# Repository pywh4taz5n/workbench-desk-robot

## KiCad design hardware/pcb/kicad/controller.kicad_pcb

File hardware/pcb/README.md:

# Controller PCB engineering package

Eight-layer controller/power-distribution board for a 48 V desk robot. The package
defines the electrical architecture, interfaces, protection, isolated CAN,
stackup, placement/thermal constraints, DFM limits, and manufacturing outputs.

## Reproduce checks

```bash
python hardware/pcb/tools/electrical_checks.py
```

The report is written to `generated/electrical_report.json`. Open
`kicad/controller.kicad_pro` with KiCad 10. The detailed EVT companion board has
117 controlled electrical components, four M3 NPTH mounting holes (121 total
footprints), fifteen SMT test pads, more than 1,300 track/via items, 31 filled copper zones,
eight copper layers, and a physical 8 mm primary/secondary isolation region.
Reproduce the controlled sources with:

```bash
<kicad>/bin/python hardware/pcb/tools/generate_footprints.py
python hardware/pcb/tools/generate_kicad_schematic.py
python hardware/pcb/tools/generate_expected_connectivity.py
python hardware/pcb/tools/generate_bom.py
<kicad>/bin/python hardware/pcb/tools/generate_kicad_board.py --session hardware/pcb/kicad/controller.ses
python hardware/pcb/tools/electrical_checks.py
python hardware/pcb/tools/audit_connectivity.py
python hardware/pcb/tools/layout_audit.py
python hardware/pcb/tools/export_fabrication.py
python hardware/pcb/tools/release_readiness.py
```

The default command is a production-release gate and returns non-zero while
the PCB remains blocked. Use `--stage evt` for prototype-order gating or
`--stage structure` when you only need the repository engineering audit.

`kicad/controller.ses` is the checked Freerouting 2.3.0 routing session. The
board generator validates every footprint position against that session before
importing the checked routing branches. Deterministic cleanup and local
supplements preserve more than 1,000 segments while adding the U2/U7 and fixture-pad migration. A
stale session cannot silently attach to moved footprints.
Generated schematic UUIDs use a resettable deterministic sequence. Board output
UUIDs are normalized after KiCad saves the file, preserving repeated references
while removing run-to-run UUID noise; routing tie-breakers use stable reference,
pad, and coordinate keys rather than process memory addresses.

The layout audit hard-gates the Q36SR U2 input, return, `12V_ISO` source and
`GND` return with separate eight-via rings on 3 x 3, 1.5 mm-pitch grids around
the THT pads, along with nominal-width coverage and bounded package escapes.
The exact 20 A manufacturer revision, lifecycle, quote, heat-spreader and AVL
remain procurement and thermal gates. The audit also requires top-layer, zero-via
oscillator routing, matched CAN via counts, and an `In1.Cu` `GND_CAN_ISO` zone
declaration. NXF1 U7 has an all-eight-layer no-track/no-via/no-pour corridor
across its 4.08 mm board pad-edge gap; this does not satisfy the 8 mm system
target or replace Safety Owner review.
CAN coupling, branch/stub geometry, reference-plane continuity, and 120 ohm field
solving remain explicit manual or supplier risks rather than being inferred from
aggregate route lengths. The report now includes per-net graph metrics, declared
reference-zone endpoint coverage, reference-layer low-speed occupancy, oscillator
length delta and load-capacitor ground-via distance, plus every accepted power-net
neckdown. These measurements bound the review; they do not claim field-solved
impedance, uninterrupted filled copper, or thermal adequacy.

Test access is separated by electrical domain: TP1 remains in the 48 V primary
region, TP2-TP5/TP8 are on the logic side, and TP6/TP7 sit beside the isolated
CAN connectors. This keeps secondary probes out of the primary test area and
avoids long CAN test stubs.
`fixture-access-plan.csv` controls the additional safety, power-good, fault,
current-monitor, and domain-reference access required by the EVT fixture. Existing
connector access is cross-checked against `connector-pinout.csv`; TP9-TP15 are
implemented as dedicated pads while every row remains fail-closed until physical
fixture evidence is attached.

The checked-in ERC and DRC reports contain zero violations and zero unconnected
items. Gerbers, drills, IPC-D-356, position data, drawings, statistics, and a
rendered inspection preview are under `fabrication/`.
`kicad/controller.kicad_dru` enforces 8 mm copper clearance between the primary
48 V domain and every non-primary net; release readiness fails if this rule is
missing even when the base DRC report is otherwise clean.

## Critical design-review correction

The original task suggestion (`TPS54160 + RT8059 + AMS1117`) is not load-capable:

- TPS54160 is a 1.5 A regulator and cannot supply the proposed 12 V motor rail.
- RT8059 is a low-current converter and cannot supply a 5 V / 8 A Jetson rail.
- AMS1117 cannot provide 3.3 V / 5 A and would exceed its thermal limit.

The baseline therefore requires a protected 48 V input and an isolated,
regulated 36-60 V-to-12 V 240 W-class module, followed by a protected 12 V / 5 A
branch to the Jetson developer-kit DC
input, and a 12-to-3.3 V 20 W synchronous buck. It deliberately does not
back-power the developer kit through a 5 V header. Design candidates are listed
in the fabrication BOM; purchase requires all independent Electrical,
Procurement, Safety and other roles named in the approval registers. System
Owner authorization alone does not create an AVL.

U2 is the `Q36SR12020NRFH` design candidate. Distributor evidence identifies
18-75 V input, 12 V/20 A and 240 W, and the checked eight-pin footprint follows
the Q36SR family mechanical drawing. The local Delta PDF is for the 12 V/19 A
variant and cannot close exact 20 A procurement evidence. `DCM3623T50M31C2T00`
remains excluded by its 16-50 V input, 28 V output and incompatible package.

The board is a companion/control board for the NVIDIA developer kit, not a raw
260-pin Jetson module carrier. See `interface-control.md` and
`source-baseline.json` for controlled interfaces, official sources, assumptions,
owners, and freeze gates. J4 is populated on this board; J7-J9 describe downstream
harness or daughterboard endpoints and are not populated in revision A.
The ISO1042 bus side uses distinct `5V_CAN_ISO` and `GND_CAN_ISO` nets supplied
by U7; neither is tied to logic ground in the board database.
The populated J4 backplane carries the external `JETSON_ENABLE_REQ` on pin 8;
it is an MCU input and is deliberately distinct from the internal
`MOTOR_ENABLE_REQ` generated on U5 pin 53. The E-stop path has distinct
`MOTOR_ENABLE_REQ` and `MOTOR_ENABLE_SAFE` nets,
a dual-channel J10 loop, dual-channel manual reset at J12, diagnostic isolation
at U8, force-guided relay candidates K1/K2, and the J11 gated output.
`connector-pinout.csv` freezes the current EVT pin mapping.
`connectors.csv` separates contact capability from the controlled system
envelope: J2 contacts are a 16 A nominal interface, but the board and harness
are limited to 10 A aggregate (120 W at 12 V) until an external branch fuse,
inrush, regeneration and fault-current analysis is approved.
`component-selection-matrix.csv` tracks every active module, the source-backed
candidate or class, verification method, owner and procurement status.
Every matrix `source_id` must resolve to a complete HTTPS source entry in
`source-baseline.json`; excluded-source records are retained as history and may
not back a design candidate.
`fabrication/bom.csv` covers every board component and its grouped lines are
recomputed deterministically. `component-approval-register.csv` defines the
required approver roles for every procurement-controlled group.
`component-approval-signatures.csv`
contains one independent row per required role, bound to the EVT revision and
fabrication-BOM SHA-256. No group is approved until every role records an
orderable MPN, datasheet revision, identity, date, and evidence reference.
Changing a summary `decision` to `APPROVED` is insufficient.
`expected-connectivity.json` and `generated/connectivity_report.json` independently
check the physical pads across all 117 controlled components, plus input-protection, CAN
isolation, current-sense and dual-channel safety invariants.
`testpoint-coverage.csv` defines the measurement, limit, instrument and required
evidence for every physical test pad.
`fabrication/bringup-test-plan.csv` covers 36 V, 48 V, and 60 V operation, UV/OV,
reverse polarity, branch short, load and regeneration transients, E-stop
discrepancy, CAN FD, and a four-hour closed-enclosure thermal soak. These are
controlled test definitions, not completed physical evidence.

Run `python hardware/pcb/tools/release_readiness.py` before sharing an order
package. The checked-in schematic is component-level and has clean ERC. EVT
prototype ordering remains blocked by AVL, safety design, supplier DFM and U2/U7
external evidence. Physical bring-up,
measured safety timing, harness execution, and verified fixture access are
separate production-release gates so prototype evidence is not a circular EVT
ordering prerequisite.
The release audit fails closed if stale U2 placeholder or excluded-part markers
appear in controlled artifacts, and separately reports whether exact manufacturer
evidence and AVL have closed.
Do not order a populated board from engineering completeness alone.

## Release status

PCB1-11 have reproducible engineering evidence. PCB12-18 have complete order,
bring-up, reliability, and production procedures but still require physical boards,
lab instruments, EMC facilities, and production operators; see the verification
matrix for the evidence that must be attached rather than inferred.

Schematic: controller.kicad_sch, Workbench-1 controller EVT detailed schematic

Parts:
C1: 1uF 100V; C_1210_3225Metric
C2: 10uF 100V; C_2220_5750Metric
C3: 470uF 25V; CP_Radial_D12.5mm_P5.00mm
C4: 1uF 25V; C_0805_2012Metric
C5: 220uF 25V; CP_Radial_D10.0mm_P5.00mm
C6: 22uF 25V; C_1210_3225Metric
C7, C8: 47uF 10V; C_1210_3225Metric
C9, C10, C11, C12, C13, C14, C15, C16, C18, C19, C40, C41, C44: 100nF; C_0603_1608Metric
C17, C42, C43: 4.7uF; C_0805_2012Metric
C20: 1uF 10V; C_0603_1608Metric
CG1: 4.7nF 100V; C_0603_1608Metric
CSS4: 22nF; C_0603_1608Metric
CY1, CY2: 18pF; C_0603_1608Metric
D1: SMCJ58A; D_SMC; MPN Littelfuse SMCJ58A
D2: CAN FD TVS; CAN_TVS; MPN Nexperia PESD2CANFD24V-T
D3, D4: FLYBACK; D_SOD-123; MPN Diodes Inc. 1N4148W-7-F
F1: 10A 125V; Fuse_4510; MPN Littelfuse 0451010.MRL
F2: PTC 0.25A; Fuse_1206_3216Metric; MPN Littelfuse 1206L025YR
J1: 48V INPUT; MicroFit_2x2; MPN Molex 43045-0412
J2: 12V MOTOR AUX; MicroFit_2x2; MPN Molex 43045-0412
J3: JETSON DEVKIT 12V; MicroFit_2x2; MPN Molex 43045-0412
J4: JETSON MCU BACKPLANE; PinHeader_2x10_P2.54mm_Vertical
J5: CAN A; MicroFit_2x2; MPN Molex 43045-0412
J6: CAN B; MicroFit_2x2; MPN Molex 43045-0412
J10: DUAL ESTOP LOOP; MicroFit_2x2; MPN Molex 43045-0412
J11: SAFETY OUTPUT; MicroFit_2x2; MPN Molex 43045-0412
J12: DUAL MANUAL RESET; MicroFit_2x2; MPN Molex 43045-0412
J13: WCH DEBUG; PinHeader_1x04_P2.54mm_Vertical
JP1: CAN TERM; PinHeader_1x02_P2.54mm_Vertical
K1: FORCE-GUIDED 12V A; Panasonic_SFM4; MPN Panasonic SFM4-DC12V
K2: FORCE-GUIDED 12V B; Panasonic_SFM4; MPN Panasonic SFM4-DC12V
L1: 100R@100MHz; ACT45B; MPN TDK ACT45B-101-2P-TL003
Q1, Q2: 150V N-MOS; Infineon_PG-TDSON-8_6.15x5.15mm; MPN Infineon BSC093N15NS5ATMA1
R30, R31, R32, R33, R34, R35, R36, R37, R38, R39, R40, R41, R42: 33R; R_0603_1608Metric
R43, R44, R45, R46, R57: 100k; R_0603_1608Metric
R47, R49, R50, R51, R54: 10k; R_0603_1608Metric
R48: 3.00k 1%; R_0603_1608Metric
R52, R53, R55, R56: 4.7k; R_0603_1608Metric
R58: 120R 1%; R_1206_3216Metric
R59: 73.2k 1%; R_0603_1608Metric
R60: 10.0k 1%; R_0603_1608Metric
RFB1: 45.0k 1%; R_0603_1608Metric
RFB2: 10.0k 1%; R_0603_1608Metric
RG1: 22k; R_0603_1608Metric
RPG1: 453k 1%; R_0603_1608Metric
RPG2: 56.0k 1%; R_0603_1608Metric
RPG3: 10k; R_0603_1608Metric
RS1: 6mR 3W 1%; Sense_3637; MPN Vishay WSL3637R0060FEA
RSH1: 510k; R_0603_1608Metric
RUV1: 19.6M 1%; R_1206_3216Metric
RUV2: 133k 1%; R_0603_1608Metric
RUV3: 162k 1%; R_0603_1608Metric
TP1: VBAT_PROTECTED; TestPoint_Pad_D1.5mm
TP2: 12V_ISO; TestPoint_Pad_D1.5mm
TP3: JETSON_12V; TestPoint_Pad_D1.5mm
TP4: 3V3_LOGIC; TestPoint_Pad_D1.5mm
TP5: GND; TestPoint_Pad_D1.5mm
TP6: CANH; TestPoint_Pad_D1.5mm
TP7: CANL; TestPoint_Pad_D1.5mm
TP8: MCU_RESET; TestPoint_Pad_D1.5mm
TP9: 5V_CAN_ISO; TestPoint_Pad_D1.5mm
TP10: 3V3_PGOOD; TestPoint_Pad_D1.5mm
TP11: JETSON_PGOOD; TestPoint_Pad_D1.5mm
TP12: JETSON_FAULT_N; TestPoint_Pad_D1.5mm
TP13: U3_IMON; TestPoint_Pad_D1.5mm
TP14: ESTOP_A_MON; TestPoint_Pad_D1.5mm
TP15: ESTOP_B_MON; TestPoint_Pad_D1.5mm
U1: LTC4368HMS-2; MSOP-10_3x3mm_P0.5mm; MPN LTC4368HMS-2#PBF
U2: 18-75V TO 12V 240W ISO; Delta_Q36SR_QuarterBrick; MPN Q36SR12020NRFH
U3: TPS26633RGE; TPS26633_RGE24; MPN Texas Instruments TPS26633RGER
U4: RPL-5.0 3V3/5A; RPL-5.0_QFN24; MPN RECOM RPL-5.0-R
U5: CH32V307VCT6; LQFP-100_14x14mm_P0.5mm; MPN WCH CH32V307VCT6
U6: ISO1042DW; ISO1042_DW16_HV; MPN Texas Instruments ISO1042DWR
U7: 3V3-5V ISO 1W; Murata_NXF1_MC; MPN NXF1S0305MC-R7
U8: ESTOP DIAGNOSTIC OPTO; SOIC-16W_7.5x10.3mm_P1.27mm; MPN Toshiba TLP293-4(GB,E)
Y1: 8MHz; Crystal_SMD_3225-4Pin_3.2x2.5mm; MPN Abracon ABM8-8.000MHZ-B2-T

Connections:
3V3_LOGIC: C7.1 (+), C8.1 (+), C9.1 (+), C10.1 (+), C11.1 (+), C12.1 (+), C13.1 (+), C14.1 (+), C15.1 (+), C16.1 (+), C17.1 (+), C40.1 (+), C42.1 (+), J4.1, J4.3, J11.4, J13.1, K1.5 (SENSE_COM), K1.9 (EDM_COM), K2.9 (EDM_COM), R47.1, R49.1, R50.1, R54.1, R55.1, R56.1, RFB1.1, RPG3.1, TP4.1, U3.12 (SHDN), U4.9 (VOUT), U4.10 (VOUT), U4.11 (VOUT), U4.12 (VOUT), U5.6 (VBAT), U5.11 (VDD), U5.21 (VREF+), U5.22 (VDDA), U5.28 (VDD), U5.50 (VIO), U5.75 (VDD), U5.100 (VIO), U6.1 (VCC1), U7.3 (+VIN)
3V3_PGOOD: TP10.1, U4.20 (PG), U4.21 (PG)
5V_CAN_ISO: C41.1 (+), C43.1 (+), C44.1 (+), TP9.1, U6.11 (VCC2), U6.16 (VCC2), U7.8 (+VOUT)
12V_ISO: C3.1 (+), C4.1 (+), C6.1 (+), F2.1 (IN), J2.1, J2.2, R46.1, R59.1, TP2.1, U2.7 (+SENSE), U2.8 (+VOUT), U3.1 (IN), U3.2 (IN), U3.5 (IN_SYS), U4.22 (VIN)
BOOT0: R43.1, U5.94 (BOOT0)
CANH: D2.1 (CANH), J5.1, J6.1, L1.4 (CANH_OUT), R58.1, TP6.1
CANH_RAW: L1.1 (CANH_IN), U6.13 (CANH)
CANL: D2.2 (CANL), J5.2, J6.2, JP1.2, L1.3 (CANL_OUT), TP7.1
CANL_RAW: L1.2 (CANL_IN), U6.12 (CANL)
CAN_RX: U5.81 (PD0/CAN1_RX), U6.5 (RXD)
CAN_TERM: JP1.1, R58.2
CAN_TX: U5.82 (PD1/CAN1_TX), U6.3 (TXD)
ESTOP_12V: F2.2 (OUT), J10.1, J10.3
ESTOP_A_MON: R49.2, TP14.1, U5.57 (PD10), U8.16 (C1)
ESTOP_B_MON: R50.2, TP15.1, U5.58 (PD11), U8.14 (C2)
ESTOP_CH_A_RETURN: J10.2, J12.1, K1.7 (HOLD_COM), U8.1 (A1)
ESTOP_CH_B_RETURN: J10.4, J12.3, K2.7 (HOLD_COM), U8.3 (A2)
ESTOP_SENSE: J4.17, J11.2, K2.6 (SENSE_NO), R57.1, U5.54 (PB15)
GND: C3.2 (-), C4.2 (-), C5.2 (-), C6.2 (-), C7.2 (-), C8.2 (-), C9.2 (-), C10.2 (-), C11.2 (-), C12.2 (-), C13.2 (-), C14.2 (-), C15.2 (-), C16.2 (-), C17.2 (-), C18.2 (-), C19.2 (-), C20.2 (-), C40.2 (-), C42.2 (-), CSS4.2 (-), CY1.2 (-), CY2.2 (-), D3.2 (A), D4.2 (A), J2.3, J2.4, J3.3, J3.4, J4.2, J4.4, J11.3, J13.4, K1.2 (COIL-), K2.2 (COIL-), R43.2, R44.2, R45.2, R48.2, R51.2, R52.2, R53.2, R57.2, R60.2, RFB2.2, RPG2.2, TP5.1, U2.4 (-VOUT), U2.5 (-SENSE), U3.7 (PLIM), U3.8 (GND), U3.25 (PowerPAD), U4.1 (PGND), U4.2 (PGND), U4.3 (PGND), U4.4 (PGND), U4.5 (PGND), U4.18 (AGND), U4.24 (PGND), U5.10 (VSS), U5.19 (VSSA), U5.20 (VREF-), U5.27 (VSS), U5.49 (VSS), U5.74 (VSS), U5.99 (VSS), U6.2 (GND1), U6.8 (GND1), U7.1 (-VIN), U8.13 (E2), U8.15 (E1)
GND_CAN_ISO: C41.2 (-), C43.2 (-), C44.2 (-), D2.3 (GND), D2.4 (GND), J5.3, J6.3, U6.9 (GND2), U6.10 (GND2), U6.15 (GND2), U7.7 (-VOUT)
GND_PWR: C1.2 (-), C2.2 (-), D1.2 (A), J1.3, J1.4, RUV3.2, U1.1 (GND), U1.2 (RETRY), U2.2 (ON/OFF), U2.3 (-VIN)
I2C_SCL: J4.16, R39.2, R55.2
I2C_SCL_MCU: R39.1, U5.92 (PB6/I2C1_SCL)
I2C_SDA: J4.15, R40.2, R56.2
I2C_SDA_MCU: R40.1, U5.93 (PB7/I2C1_SDA)
JETSON_12V: C5.1 (+), J3.1, J3.2, RPG1.1, TP3.1, U3.17 (OUT), U3.18 (OUT)
JETSON_ENABLE_REQ: J4.8, U5.91 (PB5)
JETSON_FAULT_N: R47.2, TP12.1, U3.14 (FLT)
JETSON_PGOOD: RPG3.2, TP11.1, U3.16 (PGOOD)
MCU_RESET: C19.1 (+), J4.20, R54.2, TP8.1, U5.14 (NRST)
MOTOR_CS0: J4.9, R33.2
MOTOR_CS0_MCU: R33.1, U5.35 (PB0)
MOTOR_CS1: J4.10, R34.2
MOTOR_CS1_MCU: R34.1, U5.36 (PB1)
MOTOR_CS2: J4.11, R35.2
MOTOR_CS2_MCU: R35.1, U5.47 (PB10)
MOTOR_CS3: J4.12, R36.2
MOTOR_CS3_MCU: R36.1, U5.48 (PB11)
MOTOR_CS4: J4.13, R37.2
MOTOR_CS4_MCU: R37.1, U5.51 (PB12)
MOTOR_CS5: J4.14, R38.2
MOTOR_CS5_MCU: R38.1, U5.52 (PB13)
MOTOR_ENABLE_REQ: K1.3 (SAFE_COM), U5.53 (PB14)
MOTOR_ENABLE_SAFE: J11.1, K2.4 (SAFE_NO)
OSC_IN: CY1.1 (+), U5.12 (OSC_IN), Y1.1
OSC_OUT: CY2.1 (+), U5.13 (OSC_OUT), Y1.2
OV_SET: RUV2.2, RUV3.1, U1.3 (OV)
RELAY_A_NC: K1.10 (EDM_NC), R44.1, U5.55 (PD8)
RELAY_B_NC: K2.10 (EDM_NC), R45.1, U5.56 (PD9)
RESET_CH_A_RETURN: D3.1 (K), J12.2, K1.1 (COIL+), K1.8 (HOLD_NO)
RESET_CH_B_RETURN: D4.1 (K), J12.4, K2.1 (COIL+), K2.8 (HOLD_NO)
SAFE_STAGE_A: K1.4 (SAFE_NO), K2.3 (SAFE_COM)
SENSE_STAGE_A: K1.6 (SENSE_NO), K2.5 (SENSE_COM)
SPI_MISO: J4.7, R32.2
SPI_MISO_MCU: R32.1, U5.31 (PA6/SPI1_MISO)
SPI_MOSI: J4.6, R31.2
SPI_MOSI_MCU: R31.1, U5.32 (PA7/SPI1_MOSI)
SPI_SCLK: J4.5, R30.2
SPI_SCLK_MCU: R30.1, U5.30 (PA5/SPI1_SCK)
SWCLK: J13.3, U5.76 (SWCLK)
SWDIO: J13.2, U5.72 (SWDIO)
U1_GATE: RG1.1, U1.10 (GATE)
U1_SHDN: RSH1.2, U1.6 (SHDN)
U3_DVDT: C18.1 (+), U3.9 (dVdT)
U3_ILIM: R48.1, U3.10 (ILIM)
U3_IMON: R51.1, TP13.1, U3.13 (IMON)
U3_PGTH: RPG1.2, RPG2.1, U3.15 (PGTH)
U3_UVLO: R59.2, R60.1, U3.6 (UVLO)
U4_CTRL: R46.2, U4.16 (CTRL)
U4_FB: RFB1.2, RFB2.1, U4.17 (FB)
U4_SS: CSS4.1 (+), U4.19 (SS)
U4_VCC: C20.1 (+), U4.6 (VCC)
U8_LED_A_K: R52.1, U8.2 (K1)
U8_LED_B_K: R53.1, U8.4 (K2)
UART_RX: J4.19, R42.2
UART_RX_MCU: R42.1, U5.69 (PA10/USART1_RX)
UART_TX: J4.18, R41.2
UART_TX_MCU: R41.1, U5.68 (PA9/USART1_TX)
UV_SET: RUV1.2, RUV2.1, U1.4 (UV)
VBAT_PROTECTED: C1.1 (+), C2.1 (+), RS1.2, TP1.1, U1.8 (VOUT), U2.1 (+VIN)
VBAT_RAW: F1.1 (IN), J1.1, J1.2

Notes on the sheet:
INPUT PROTECTION
ISOLATED POWER
JETSON EFUSE
3V3 POWER
POWER OUTPUTS
MCU AND BACKPLANE
ISOLATED CAN FD
HARDWIRED ESTOP
TEST ACCESS

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
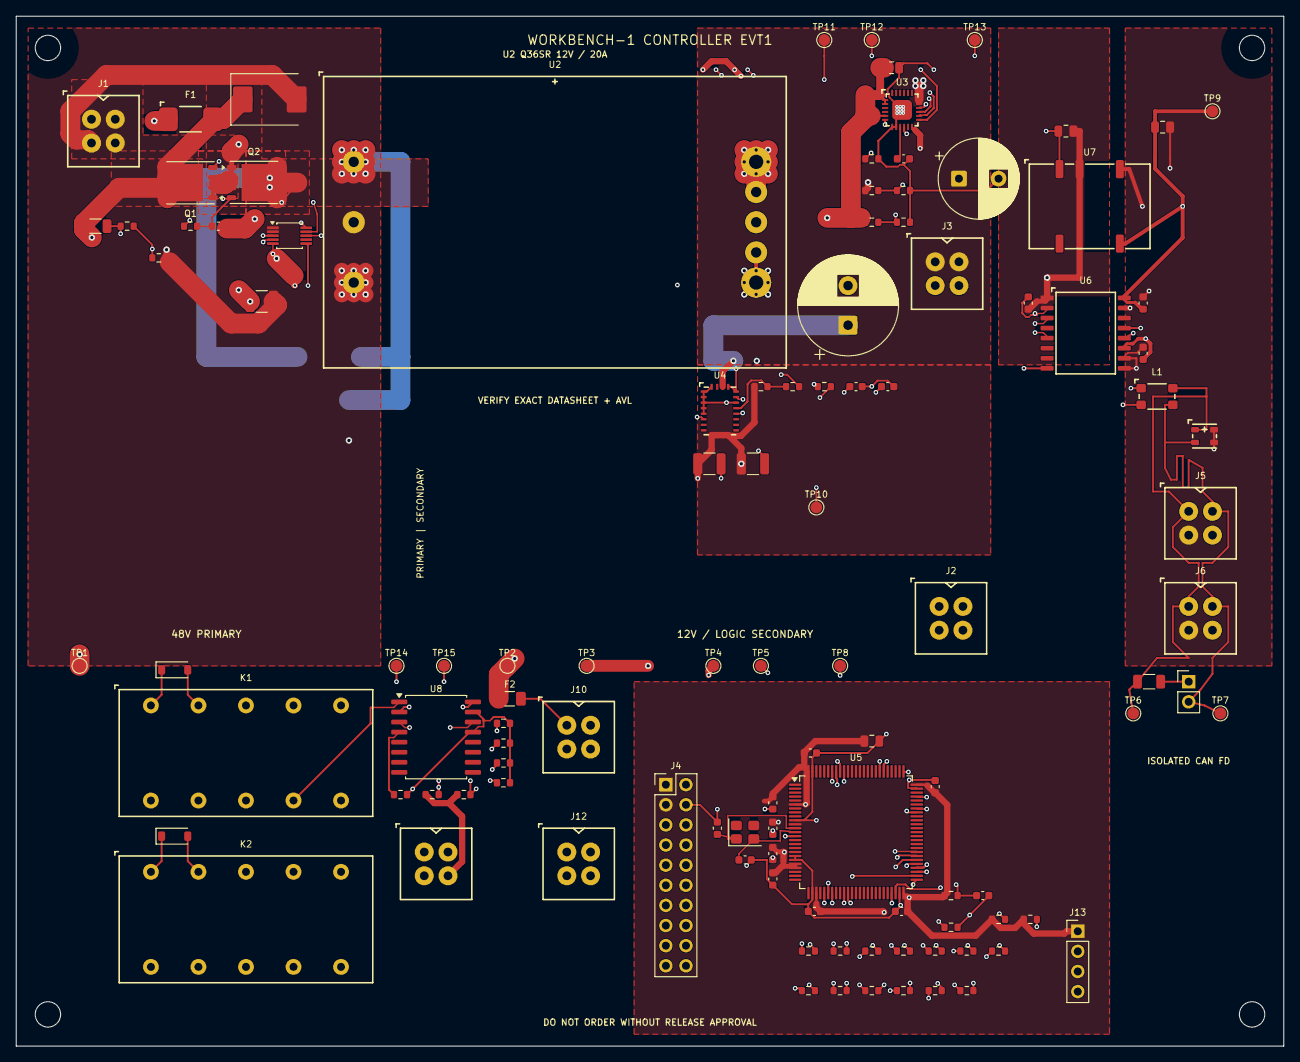
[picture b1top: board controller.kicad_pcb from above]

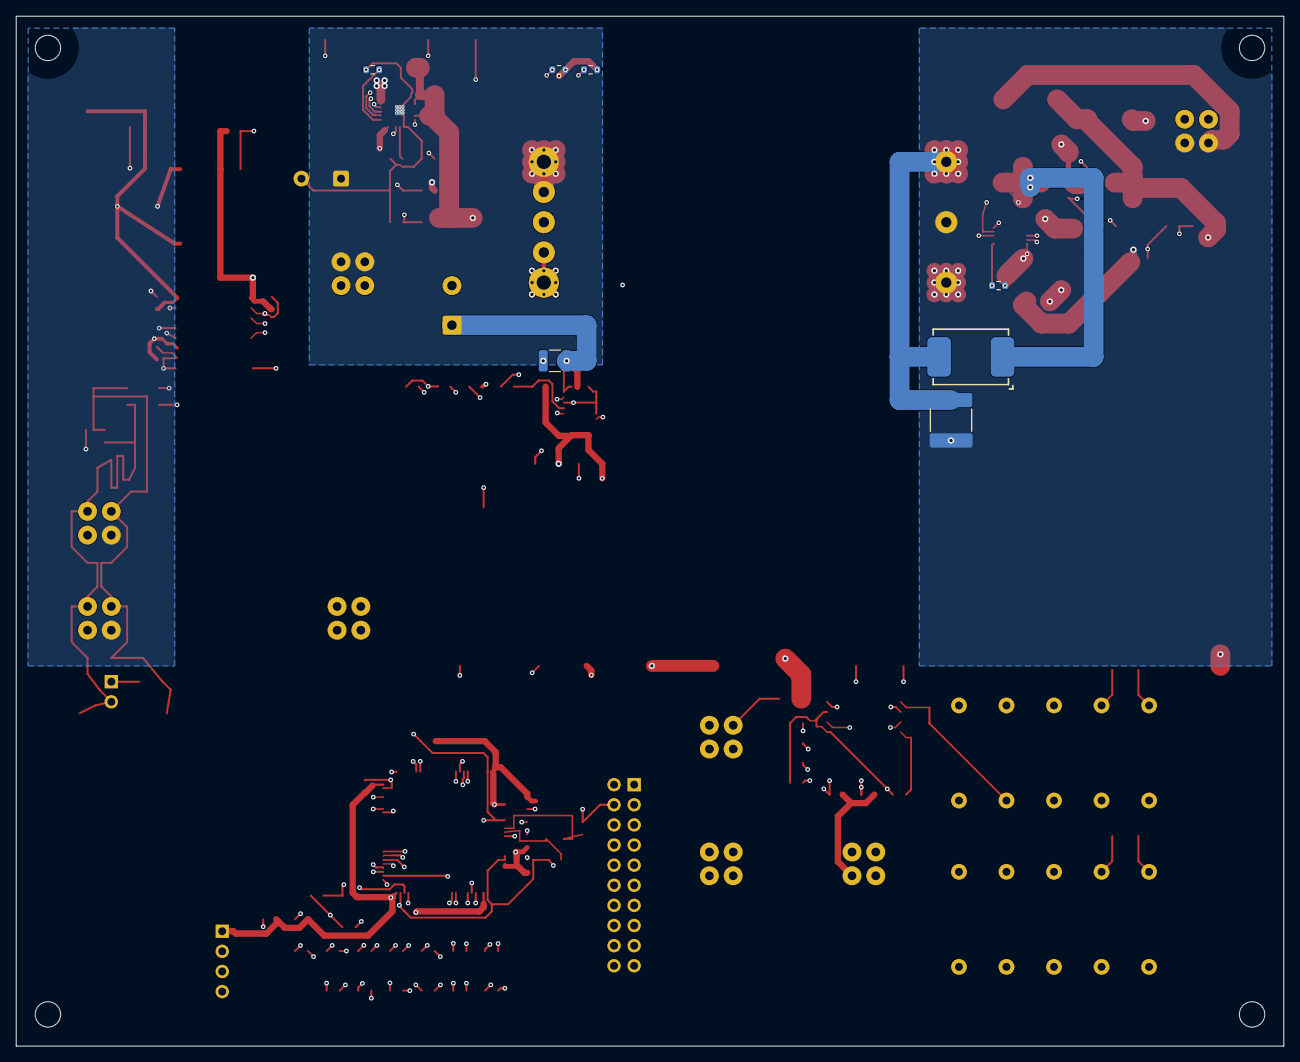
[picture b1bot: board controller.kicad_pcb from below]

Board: 8 copper layers, 160.0 x 130.0 mm, 121 parts (7 on the bottom side), 85 nets.

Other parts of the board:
H1, H2, H3, H4: M3_NPTH

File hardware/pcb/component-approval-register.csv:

reference,candidate,required_approver,decision,approved_mpn,datasheet_revision,approved_by,approved_at,evidence_ref
C1,1uF 100V; Capacitor_SMD:C_1210_3225Metric,Electrical + Procurement Owners,PENDING,,,,,
C2,10uF 100V; Capacitor_SMD:C_2220_5750Metric,Electrical + Procurement Owners,PENDING,,,,,
C3,470uF 25V; Capacitor_THT:CP_Radial_D12.5mm_P5.00mm,Electrical + Procurement Owners,PENDING,,,,,
C4,1uF 25V; Capacitor_SMD:C_0805_2012Metric,Electrical + Procurement Owners,PENDING,,,,,
C5,220uF 25V; Capacitor_THT:CP_Radial_D10.0mm_P5.00mm,Electrical + Procurement Owners,PENDING,,,,,
C6,22uF 25V; Capacitor_SMD:C_1210_3225Metric,Electrical + Procurement Owners,PENDING,,,,,
C7 C8,47uF 10V; Capacitor_SMD:C_1210_3225Metric,Electrical + Procurement Owners,PENDING,,,,,
C9 C10 C11 C12 C13 C14 C15 C16 C19,100nF; Capacitor_SMD:C_0603_1608Metric,Firmware + Electrical + Procurement Owners,PENDING,,,,,
C17,4.7uF; Capacitor_SMD:C_0805_2012Metric,Firmware + Electrical + Procurement Owners,PENDING,,,,,
C18,100nF; Capacitor_SMD:C_0603_1608Metric,Electrical + Procurement Owners,PENDING,,,,,
C20,1uF 10V; Capacitor_SMD:C_0603_1608Metric,Electrical + Procurement Owners,PENDING,,,,,
C40 C41 C44,100nF; Capacitor_SMD:C_0603_1608Metric,Electrical + Procurement Owners,PENDING,,,,,
C42 C43,4.7uF; Capacitor_SMD:C_0805_2012Metric,Electrical + Procurement Owners,PENDING,,,,,
CG1,4.7nF 100V; Capacitor_SMD:C_0603_1608Metric,Electrical + Procurement Owners,PENDING,,,,,
CSS4,22nF; Capacitor_SMD:C_0603_1608Metric,Electrical + Procurement Owners,PENDING,,,,,
CY1 CY2,18pF; Capacitor_SMD:C_0603_1608Metric,Firmware + Electrical + Procurement Owners,PENDING,,,,,
D1,Littelfuse SMCJ58A,Electrical + Procurement Owners,PENDING,,,,,
D2,Nexperia PESD2CANFD24V-T,Electrical + Procurement Owners,PENDING,,,,,
D3 D4,Diodes Inc. 1N4148W-7-F,Safety + Electrical + Procurement Owners,PENDING,,,,,
F1,Littelfuse 0451010.MRL,Electrical + Procurement Owners,PENDING,,,,,
F2,Littelfuse 1206L025YR,Safety + Electrical + Procurement Owners,PENDING,,,,,
J1,Molex 43045-0412,System + Electrical + Procurement Owners,PENDING,,,,,
J2,Molex 43045-0412,Electrical + Procurement Owners,PENDING,,,,,
J3,Molex 43045-0412,System + Electrical + Procurement Owners,PENDING,,,,,
J4,JETSON MCU BACKPLANE; Connector_PinHeader_2.54mm:PinHeader_2x10_P2.54mm_Vertical,Firmware + Electrical + Procurement Owners,PENDING,,,,,
J5,Molex 43045-0412,Electrical + Procurement Owners,PENDING,,,,,
J6,Molex 43045-0412,Electrical + Procurement Owners,PENDING,,,,,
J10,Molex 43045-0412,Safety + Electrical + Procurement Owners,PENDING,,,,,
J11,Molex 43045-0412,Safety + Electrical + Procurement Owners,PENDING,,,,,
J12,Molex 43045-0412,Safety + Electrical + Procurement Owners,PENDING,,,,,
J13,WCH DEBUG; Connector_PinHeader_2.54mm:PinHeader_1x04_P2.54mm_Vertical,Firmware + Electrical + Procurement Owners,PENDING,,,,,
JP1,CAN TERM; Connector_PinHeader_2.54mm:PinHeader_1x02_P2.54mm_Vertical,Electrical + Procurement Owners,PENDING,,,,,
K1,Panasonic SFM4-DC12V,Safety + Electrical + Procurement Owners,PENDING,,,,,
K2,Panasonic SFM4-DC12V,Safety + Electrical + Procurement Owners,PENDING,,,,,
L1,TDK ACT45B-101-2P-TL003,Electrical + Procurement Owners,PENDING,,,,,
Q1 Q2,Infineon BSC093N15NS5ATMA1,Electrical + Procurement Owners,PENDING,,,,,
R30 R31 R32 R33 R34 R35 R36 R37 R38 R39 R40 R41 R42,33R; Resistor_SMD:R_0603_1608Metric,Firmware + Electrical + Procurement Owners,PENDING,,,,,
R43,100k; Resistor_SMD:R_0603_1608Metric,Firmware + Electrical + Procurement Owners,PENDING,,,,,
R44 R45 R57,100k; Resistor_SMD:R_0603_1608Metric,Safety + Electrical + Procurement Owners,PENDING,,,,,
R46,100k; Resistor_SMD:R_0603_1608Metric,Electrical + Procurement Owners,PENDING,,,,,
R47 R51 RPG3,10k; Resistor_SMD:R_0603_1608Metric,Electrical + Procurement Owners,PENDING,,,,,
R48,3.00k 1%; Resistor_SMD:R_0603_1608Metric,Electrical + Procurement Owners,PENDING,,,,,
R49 R50,10k; Resistor_SMD:R_0603_1608Metric,Safety + Electrical + Procurement Owners,PENDING,,,,,
R52 R53,4.7k; Resistor_SMD:R_0603_1608Metric,Safety + Electrical + Procurement Owners,PENDING,,,,,
R54,10k; Resistor_SMD:R_0603_1608Metric,Firmware + Electrical + Procurement Owners,PENDING,,,,,
R55 R56,4.7k; Resistor_SMD:R_0603_1608Metric,Firmware + Electrical + Procurement Owners,PENDING,,,,,
R58,120R 1%; Resistor_SMD:R_1206_3216Metric,Electrical + Procurement Owners,PENDING,,,,,
R59,73.2k 1%; Resistor_SMD:R_0603_1608Metric,Electrical + Procurement Owners,PENDING,,,,,
R60,10.0k 1%; Resistor_SMD:R_0603_1608Metric,Electrical + Procurement Owners,PENDING,,,,,
RFB1,45.0k 1%; Resistor_SMD:R_0603_1608Metric,Electrical + Procurement Owners,PENDING,,,,,
RFB2,10.0k 1%; Resistor_SMD:R_0603_1608Metric,Electrical + Procurement Owners,PENDING,,,,,
RG1,22k; Resistor_SMD:R_0603_1608Metric,Electrical + Procurement Owners,PENDING,,,,,
RPG1,453k 1%; Resistor_SMD:R_0603_1608Metric,Electrical + Procurement Owners,PENDING,,,,,
RPG2,56.0k 1%; Resistor_SMD:R_0603_1608Metric,Electrical + Procurement Owners,PENDING,,,,,
RS1,Vishay WSL3637R0060FEA,Electrical + Procurement Owners,PENDING,,,,,
RSH1,510k; Resistor_SMD:R_0603_1608Metric,Electrical + Procurement Owners,PENDING,,,,,
RUV1,19.6M 1%; Resistor_SMD:R_1206_3216Metric,Electrical + Procurement Owners,PENDING,,,,,
RUV2,133k 1%; Resistor_SMD:R_0603_1608Metric,Electrical + Procurement Owners,PENDING,,,,,
RUV3,162k 1%; Resistor_SMD:R_0603_1608Metric,Electrical + Procurement Owners,PENDING,,,,,
U1,LTC4368HMS-2#PBF,Electrical + Procurement Owners,PENDING,,,,,
U2,Q36SR12020NRFH,Electrical + Procurement Owners,PENDING,,,,,
U3,Texas Instruments TPS26633RGER,Electrical + Procurement Owners,PENDING,,,,,
U4,RECOM RPL-5.0-R,Electrical + Procurement Owners,PENDING,,,,,
U5,WCH CH32V307VCT6,Firmware + Electrical + Procurement Owners,PENDING,,,,,
U6,Texas Instruments ISO1042DWR,Electrical + Procurement Owners,PENDING,,,,,
U7,NXF1S0305MC-R7,Electrical + Safety + Procurement Owners,PENDING,,,,,
U8,"Toshiba TLP293-4(GB,E)",Safety + Electrical + Procurement Owners,PENDING,,,,,
Y1,Abracon ABM8-8.000MHZ-B2-T,Firmware + Electrical + Procurement Owners,PENDING,,,,,
